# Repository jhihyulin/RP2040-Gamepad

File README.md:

# RP2040-Gamepad

⚠️In development⚠️(On hold, waiting for [Full analog support#294](https://github.com/orgs/OpenStickCommunity/projects/1/views/1?pane=issue&itemId=29330840) done)

[Raspberry Pi Pico](https://www.raspberrypi.com/products/raspberry-pi-pico/) + [GP2040-CE](https://github.com/OpenStickCommunity/GP2040-CE)

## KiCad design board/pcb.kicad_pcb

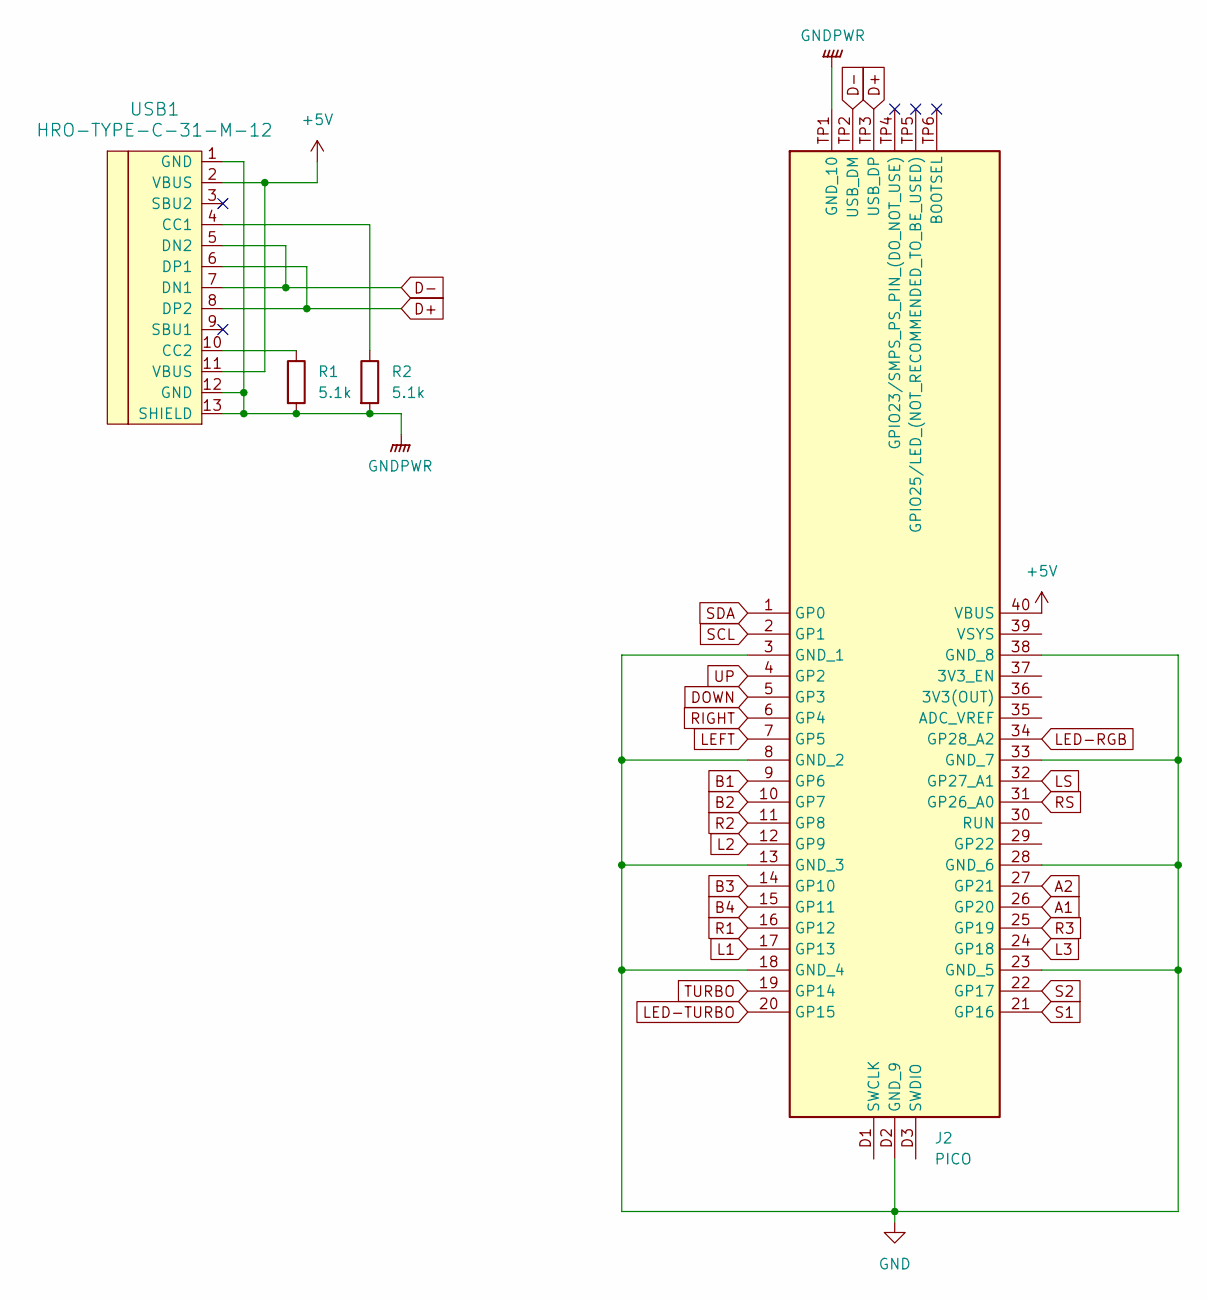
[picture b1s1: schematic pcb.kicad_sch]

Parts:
J2: PICO; Manufacturer_Part_Number PICO
R1, R2: 5.1k; R_0603_1608Metric_Pad0.98x0.95mm_HandSolder
USB1: HRO-TYPE-C-31-M-12; HRO-TYPE-C-31-M-12-HandSoldering

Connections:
+5V: J2.40 (VBUS), USB1.2 (VBUS), USB1.11 (VBUS)
A1: J2.26 (GP20)
A2: J2.27 (GP21)
B1: J2.9 (GP6)
B2: J2.10 (GP7)
B3: J2.14 (GP10)
B4: J2.15 (GP11)
D+: J2.TP3 (USB_DP), USB1.6 (DP1), USB1.8 (DP2)
D-: J2.TP2 (USB_DM), USB1.5 (DN2), USB1.7 (DN1)
DOWN: J2.5 (GP3)
GND: J2.3 (GND_1), J2.8 (GND_2), J2.13 (GND_3), J2.18 (GND_4), J2.23 (GND_5), J2.28 (GND_6), J2.33 (GND_7), J2.38 (GND_8), J2.D2 (GND_9)
GNDPWR: J2.TP1 (GND_10), R1.2, R2.2, USB1.1 (GND), USB1.12 (GND), USB1.13 (SHIELD)
L1: J2.17 (GP13)
L2: J2.12 (GP9)
L3: J2.24 (GP18)
LED-RGB: J2.34 (GP28_A2)
LED-TURBO: J2.20 (GP15)
LEFT: J2.7 (GP5)
LS: J2.32 (GP27_A1)
unnamed: R2.1, USB1.4 (CC1)
unnamed: R1.1, USB1.10 (CC2)
R1: J2.16 (GP12)
R2: J2.11 (GP8)
R3: J2.25 (GP19)
RIGHT: J2.6 (GP4)
RS: J2.31 (GP26_A0)
S1: J2.21 (GP16)
S2: J2.22 (GP17)
SCL: J2.2 (GP1)
SDA: J2.1 (GP0)
TURBO: J2.19 (GP14)
UP: J2.4 (GP2)

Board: 2 copper layers, 4 parts (0 on the bottom side), 7 nets, no tracks yet.

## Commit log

2023-07-08 [Update] README.md
2023-07-09 [Add] USB-C Connecter
